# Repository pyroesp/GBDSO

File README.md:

# GBDSO

GBDSO Website : http://swelectronics.co.uk/Gameboy/DsoDemo/DsoDemo.htm  
GBDSO Elektor article : http://www.radanpro.com/Radan2400/TestShematics/GameBoyScope.pdf  
GBDSO BOM list (2019/02) : https://docs.google.com/spreadsheets/d/1vu9Xc1Mw5STfz_mAsAOrmmyRrHJMRS4_JKM7iif-KBE/edit#gid=0  

## Max Voltage Ratings

- +/- 16V on 1:1  
- +/- 50V on 10:1  

Do **NOT** exceed the max voltage ratings or you risk damaging the cartridge and the Game Boy.  
I'm not responsible if it blows up!  

## Schematic

## PCB

## Game Boy test

Since the big v2 update on 2021/01/08, this GBDSO board works on both channels.  
See pictures below:  

## Official game cart dimensions

Below you'll find the dimensions for the PCB of an official game (Pokémon Yellow JAP).  

## Programming the AT27C256R

The first jumper JP1 selects either 5V to pin 2 of the PROM (VPP) and VPP from the unused 5th edge connector.  

The second jumper JP2 cuts the power going to the rest of the board.  
While in programming mode, the PROM needs 6.5V to VCC and I'd rather not have it power to the rest of the board.  

To program the PROM, leave JP2 open and set JP1 so that the edge connector VPP is connected to the PROM VPP.  
When programming is done, bridge JP2 and set JP1 so that 5V go to the PROM VPP.  

## GBDSO PROM to PDIP28  

Any decent Universal Programmer should be able to program the PROM on the cart.  
You can see the adapter board on the 3D rendered board above.  

The Game Boy connector uses the Xunbeifang GNI172 footprint made by **obskyr** from the <a href="https://github.com/gbdev/awesome-gbdev">gbdev discord</a>.  
You can find other Game Boy connectors made by **Gekkio** here: <a href="https://github.com/Gekkio/gekkio-kicad-libs">gekkio-kicad-libs</a>.  

The Xunbeifang GNI172 can be found on <a href="https://www.aliexpress.com/item/For-Nintendo-DS-NDSL-GBA-Game-Cartridge-Card-Reader-Slot-Repair-Part/32679592016.html">aliexpress</a>.

To program the PROM, leave JP1 open and close JP2 as shown below.

Plug the adapter board into a Universal Programmer and set the target device to DIP28 AT27C256R.

Note: This part of the board has not been tested yet, so I hope it works.

## Original GBDSO

Original GBDSO pictures from November 2000 courtesy of **Tauwasser** on the <a href="https://github.com/gbdev/awesome-gbdev">gbdev discord</a>.

## BOM list

|                       Label                        |               Value / Name               | Price per unit | Number | Total Price |                                                     Link                                                     |
|----------------------------------------------------|------------------------------------------|----------------|--------|-------------|--------------------------------------------------------------------------------------------------------------|
| R1, R2, R4, R8, R9, R11                                 | 1M                                       |           0.09 |      6 |        0.54 | https://www.digikey.be/product-detail/en/bourns-inc/CR0805-FX-1004ELF/CR0805-FX-1004ELFCT-ND/3740924         |
| R15                                                | 15k                                      |           0.09 |      1 |        0.09 | https://www.digikey.be/product-detail/en/bourns-inc/CR0805-FX-1502ELF/CR0805-FX-1502ELFCT-ND/3740926         |
| R5, R12                                             | 470k                                     |           0.09 |      2 |        0.18 | https://www.digikey.be/product-detail/en/RC0805FR-07470KL/311-470KCRCT-ND/730924/?itemSeq=284203171          |
| R3, R6, R7, R10, R13, R14                               | 4k7                                      |           0.09 |      6 |        0.54 | https://www.digikey.be/product-detail/en/CR0805-FX-4701ELF/CR0805-FX-4701ELFCT-ND/3925402/?itemSeq=284203192 |
| R16, R17                                            | 100k                                     |           0.09 |      2 |        0.18 | https://www.digikey.be/product-detail/en/yageo/RC0805FR-07100KL/311-100KCRCT-ND/730491                       |
| P1, P2                                              | 100k                                     |           0.24 |      2 |        0.48 | https://www.digikey.be/product-detail/en/bourns-inc/TC33X-2-104E/TC33X-104ECT-ND/612912                      |
| C1, C10                                             | 18p                                      |           0.12 |      2 |        0.24 | https://www.digikey.be/product-detail/en/yageo/CC0805JRNPO9BN180/311-1102-1-ND/303012                        |
| C2, C4, C5, C8, C9, C11, C12, C14, C17-C21, C23, C27, C29, C30 | 100n                                     |           0.09 |     17 |        1.53 | https://www.digikey.be/product-detail/en/CL21B104KBCNNNC/1276-1003-1-ND/3889089/?itemSeq=284204783           |
| C3, C13                                             | 1p8                                      |           0.09 |      2 |        0.18 | https://www.digikey.be/product-detail/en/samsung-electro-mechanics/CL21C1R8CBANNNC/1276-2599-1-ND/3890685    |
| C6, C15                                             | 15p                                      |            0.1 |      2 |         0.2 | https://www.digikey.be/product-detail/en/wurth-electronics-inc/885012007052/732-7847-1-ND/5454474            |
| C7, C16                                             | 220p                                     |           0.09 |      2 |        0.18 | https://www.digikey.be/product-detail/en/CL21B221KBANNNC/1276-2474-1-ND/3890560/?itemSeq=284205074           |
| C22, C24, C25, C26, C28, C31, C33                        | 10µ 16V                                  |           0.31 |      7 |        2.17 | https://www.digikey.be/product-detail/en/vishay-sprague/293D106X0016A2TE3/718-1956-1-ND/3985805              |
| L1, L2, L3                                           | 100µ                                     |           0.18 |      3 |        0.54 | https://www.digikey.be/product-detail/en/taiyo-yuden/LBM2016T101J/587-1817-1-ND/1465287                      |
| D1, D2                                              | BAV199                                   |           0.17 |      2 |        0.34 | https://www.digikey.be/product-detail/en/diodes-incorporated/BAV199-7-F/BAV199-FDICT-ND/1033647              |
| D3                                                 | ZR25D01 -> ZR40402F25TA                  |           0.61 |      1 |        0.61 | https://www.digikey.be/product-detail/en/diodes-incorporated/ZR40402F25TA/ZR40402F25TACT-ND/243209           |
| IC1, IC3                                            | MC33182D -> TL072CDT                     |           0.42 |      2 |        0.84 | https://www.digikey.com/product-detail/en/stmicroelectronics/TL072CDT/497-2200-1-ND/599107                   |
| IC2                                                | DS1267S100 -> DS1267BS-100+              |           5.52 |      1 |        5.52 | https://www.digikey.be/product-detail/en/maxim-integrated/DS1267BS-100/DS1267BS-100-ND/5049982               |
| IC4                                                | MAX114CAG                                |            6.9 |      1 |         6.9 | https://www.digikey.be/product-detail/en/maxim-integrated/MAX114CAG/MAX114CAG-ND/1428095                     |
| IC5                                                | 74HC175D                                 |           0.41 |      1 |        0.41 | https://www.digikey.be/product-detail/en/texas-instruments/SN74HC175DR/296-14840-1-ND/562676                 |
| IC6                                                | 74HC138D                                 |           0.34 |      1 |        0.34 | https://www.digikey.be/product-detail/en/texas-instruments/SN74HC138D/296-1193-5-ND/277220                   |
| IC7                                                | AT27C256R-12JC -> AT27C256R-70JU         |            1.2 |      1 |         1.2 | https://www.digikey.be/product-detail/en/microchip-technology/AT27C256R-70JU/AT27C256R-70JU-ND/1008583       |
| IC8                                                | TLC27L2CD                                |           0.86 |      1 |        0.86 | https://www.digikey.be/product-detail/en/texas-instruments/TLC27L2CDR/296-1316-1-ND/404950                   |
| IC9                                                | MAX828EUK                                |            4.5 |      1 |         4.5 | https://www.digikey.be/product-detail/en/MAX828EUK%2bT/MAX828EUK%2bTCT-ND/2699369/?itemSeq=284207452         |
| S1, S2                                              | Slide switch 1 change-over contact |           0.49 |      2 |        0.98 | https://www.digikey.be/product-detail/en/c-k/JS102011SAQN/401-1999-1-ND/1640114                              |
| K1, K2                                              | 3.5mm stereo socket -> mono smd          |           0.88 |      2 |        1.76 | https://www.digikey.be/product-detail/en/cui-inc/MJ-3523-SMT-TR/CP-3523MJCT-ND/669691                        |

Total Price: 31.31€<br>			
Total Components: 70

## Replacement parts

The input opamps MC33182D is not being sold anymore, at least not on digikey.  
So looking around I thought the TL062 would be a nice replacement but the numbers weren't quite similar.  
I've looked at the TL072 and this one looks pretty good, the only downside is that it isn't a low power opamp.  

If we compare the current consumption from the TL072 and the MC33182D, the TL072 uses 5 times more current (1.4mA typ.) than the MC33182D (420µA).  

Looking further into the MC33182D I found this old forum post talking about replacing it on a GBDSO : [edaboard forum](https://www.edaboard.com/showthread.php?40716-Need-alternative-for-MC33182D-(dual-opamp)-for-GBDSO&highlight=gbdso)  
They talked about the TL082, LF412, TLE2082A and TLE2602. Someone used that last one as a replacement for the MC33182D, although digikey has it priced at around 2$ per unit...  

Looking at the information page on TI's website, this is what they say:  
> The TL206x devices are pin-compatible with other TI BiFETs; they can be used to double the bandwidth of TL06x and TL03x circuits, or to reduce power consumption of TL05x, TL07x, and TL08x circuits by nearly 90%.  

That power reduction is crucial for long lasting batteries.  
For now though, I'll try the TL062 I currently have and will try the TL072 on a later date.  
I'll also try to find a suitable, pin-compatible, low power replacement opamp for the TL072.

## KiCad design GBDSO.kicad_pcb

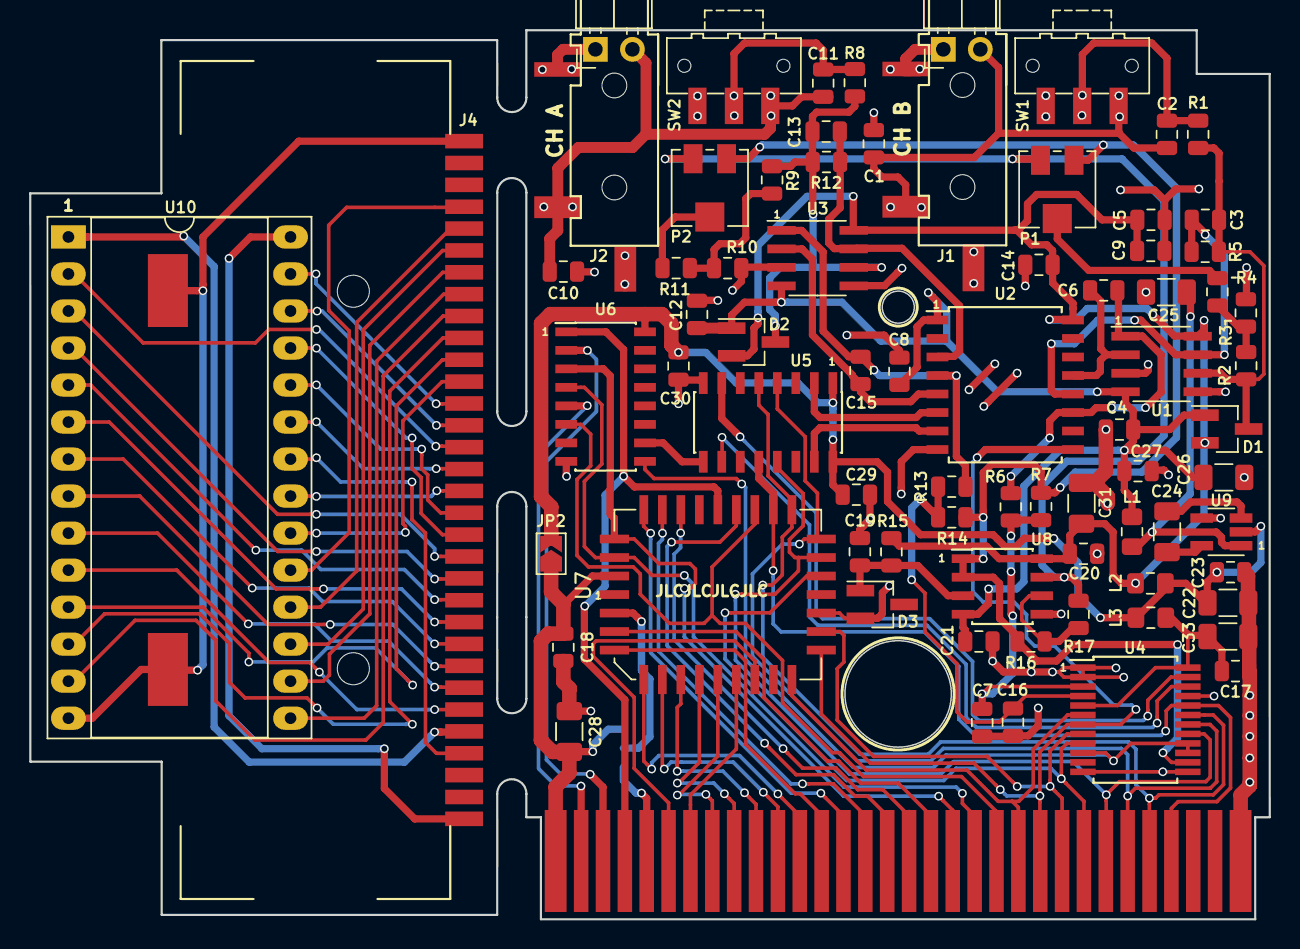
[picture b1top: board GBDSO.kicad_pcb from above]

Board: 2 copper layers, 85.0 x 61.0 mm, 77 parts (1 on the bottom side), 92 nets.

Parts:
C1, C10: 18p; C_0805_2012Metric
C2, C4, C5, C8, C9, C11, C12, C14, C17, C18, C19, C20, C21, C23, C27, C29, C30: 100n; C_0805_2012Metric
C3, C13: 1p8; C_0805_2012Metric
C6, C15: 15p; C_0805_2012Metric
C7, C16: 220p; C_0805_2012Metric
C22, C24, C25, C26, C28, C31, C33: 10µ; C_1206_3216Metric
D1, D2: BAV199; SOT-23_Handsoldering
D3: ZR4040-2.5; SOT-23_Handsoldering
J1, J2: MJ-3523-SMT-TR
J3: EdgeConnector; GB_EdgeConnector
J4: GameBoy Cartridge Connector; Game_Boy_Cartridge_Slot_Xunbeifang_GNI172
J5, J6: Conn_01x02; PinHeader_1x02_P2.54mm_Horizontal
JP1: SolderJumper_3_Open; SolderJumper-3_P1.3mm_Open_RoundedPad1.0x1.5mm_NumberLabels
JP2: SolderJumper_2_Open; SolderJumper-2_P1.3mm_Open_TrianglePad1.0x1.5mm
L1, L2, L3: 100µ; L_0805_2012Metric_Pad1.15x1.40mm_HandSolder
P1, P2: 100k; Potentiometer_Vishay_TS53YJ_Vertical
R1, R2, R4, R8, R9, R11: 1M; R_0805_2012Metric
R3, R6, R7, R10, R13, R14: 4k7; R_0805_2012Metric
R5, R12: 470k; R_0805_2012Metric
R15: 15k; R_0805_2012Metric
R16, R17: 100k; R_0805_2012Metric
SW1, SW2: SW_SPDT; SW_SPDT_CK-JS102011SAQN
U1, U3: TL072; SOIC-8_3.9x4.9mm_P1.27mm
U2: DS1267_SOIC; SOIC-16W_7.5x10.3mm_P1.27mm
U4: MAX114CAG; SSOP-24_5.3x8.2mm_P0.65mm
U5: 74HC175D; SOIC-16_3.9x9.9mm_P1.27mm
U6: 74HC138D; SOIC-16_3.9x9.9mm_P1.27mm
U7: AT27C256R; PLCC-32_HandSolder
U8: TLC272; SOIC-8_3.9x4.9mm_P1.27mm
U9: MAX828; SOT-23-5_HandSoldering
U10: AT27C256R-PDIP28; DIP-28_W15.24mm_Socket_LongPads

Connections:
+2.5V: P1.3, P2.3, R7.2, R14.2, R16.2, U4.14, U8.1, U8.2
+5V: C18.1, C22.1, C23.1, C28.1, C29.1, C30.1, J3.1, JP1.3, JP2.1, JP2.2, L2.1, L3.1, U5.1, U5.16, U6.16, U7.32, U9.2
+5VA: C5.1, C9.1, C14.1, C20.1, C31.1, D1.2, D2.2, L2.2, R15.2, U1.8, U2.16, U3.8, U8.8
+5VC: C17.1, C33.1, L3.2, U4.5, U4.24
-2.5V: P1.1, P2.1, R17.1, U8.7
-5V: C4.2, C8.1, C12.2, C21.1, C26.1, C27.1, D1.1, D2.1, L1.2, U1.4, U2.1, U3.4, U8.4
/GBDSO Cartridge/A0: J3.6, U7.11
/GBDSO Cartridge/A1: J3.7, U7.10
/GBDSO Cartridge/A2: J3.8, U7.9
/GBDSO Cartridge/A3: J3.9, U7.8
/GBDSO Cartridge/A4: J3.10, U7.7
/GBDSO Cartridge/A5: J3.11, U7.6
/GBDSO Cartridge/A6: J3.12, U7.5
/GBDSO Cartridge/A7: J3.13, U7.4
/GBDSO Cartridge/A8: J3.14, U7.29
/GBDSO Cartridge/A9: J3.15, U7.28
/GBDSO Cartridge/A10: J3.16, U7.24
/GBDSO Cartridge/A11: J3.17, U7.27
/GBDSO Cartridge/A12: J3.18, U7.3
/GBDSO Cartridge/A13: J3.19, U6.3, U7.30
/GBDSO Cartridge/A14: J3.20, U6.4, U7.31
/GBDSO Cartridge/A15: J3.21, U6.6, U7.23
/GBDSO Cartridge/D0: J3.22, U4.6, U7.13
/GBDSO Cartridge/D1: J3.23, U2.9, U4.7, U7.14
/GBDSO Cartridge/D2: J3.24, U4.8, U7.15
/GBDSO Cartridge/D3: J3.25, U4.9, U7.18
/GBDSO Cartridge/D4: J3.26, U4.17, U5.13, U7.19
/GBDSO Cartridge/D5: J3.27, U4.18, U5.4, U7.20
/GBDSO Cartridge/D6: J3.28, U4.19, U5.5, U7.21
/GBDSO Cartridge/D7: J3.29, U4.20, U5.12, U7.22
/GBDSO Cartridge/ECLK: J3.2, U6.5
/GBDSO Cartridge/VPP: J3.5, JP1.1
/GBDSO Cartridge/~RD: J3.4, U6.1, U7.25
/GBDSO Cartridge/~WR: J3.3, U6.2
/GBDSO EPROM Adapter Board/A0: J4.6, U10.10
/GBDSO EPROM Adapter Board/A1: J4.7, U10.9
/GBDSO EPROM Adapter Board/A2: J4.8, U10.8
/GBDSO EPROM Adapter Board/A3: J4.9, U10.7
/GBDSO EPROM Adapter Board/A4: J4.10, U10.6
/GBDSO EPROM Adapter Board/A5: J4.11, U10.5
/GBDSO EPROM Adapter Board/A6: J4.12, U10.4
/GBDSO EPROM Adapter Board/A7: J4.13, U10.3
/GBDSO EPROM Adapter Board/A8: J4.14, U10.25
/GBDSO EPROM Adapter Board/A9: J4.15, U10.24
/GBDSO EPROM Adapter Board/A10: J4.16, U10.21
/GBDSO EPROM Adapter Board/A11: J4.17, U10.23
/GBDSO EPROM Adapter Board/A12: J4.18, U10.2
/GBDSO EPROM Adapter Board/A13: J4.19, U10.26
/GBDSO EPROM Adapter Board/A14: J4.20, U10.27
/GBDSO EPROM Adapter Board/A15: J4.21, U10.20
/GBDSO EPROM Adapter Board/D0: J4.22, U10.11
/GBDSO EPROM Adapter Board/D1: J4.23, U10.12
/GBDSO EPROM Adapter Board/D2: J4.24, U10.13
/GBDSO EPROM Adapter Board/D3: J4.25, U10.15
/GBDSO EPROM Adapter Board/D4: J4.26, U10.16
/GBDSO EPROM Adapter Board/D5: J4.27, U10.17
/GBDSO EPROM Adapter Board/D6: J4.28, U10.18
/GBDSO EPROM Adapter Board/D7: J4.29, U10.19
/GBDSO EPROM Adapter Board/VCC: J4.1, U10.28
/GBDSO EPROM Adapter Board/VPP: J4.5, U10.1
/GBDSO EPROM Adapter Board/~RD: J4.4, U10.22
GND: C1.2, C4.1, C5.2, C7.2, C8.2, C9.2, C10.2, C12.1, C14.2, C16.2, C17.2, C18.2, C19.2, C20.2, C21.2, C22.2, C23.2, C25.2, C26.2, C27.2, C28.2, C29.2, C30.2, C31.2, C33.2, D3.2, J1.1, J2.1, J3.32, J4.32, J5.1, J6.1, R3.1, R10.1, U1.3, U1.5, U2.8, U3.3, U3.5, U4.1, U4.2, U4.12, U4.13, U4.21, U5.8, U6.8, U7.16, U8.5, U9.4, U10.14
unnamed: C1.1, C2.1, J1.2, J5.2, SW1.1
unnamed: C2.2, R1.2, SW1.2
unnamed: C3.1, D1.3, R1.1, R2.2, R5.2, U1.6
unnamed: C3.2, R5.1, U1.7, U2.12
unnamed: C6.1, U1.2, U2.13
unnamed: C6.2, R6.2, U1.1, U2.11
unnamed: C7.1, R6.1, R7.1, U4.3
unnamed: C10.1, C11.2, J2.2, J6.2, SW2.1
unnamed: C11.1, R8.2, SW2.2
unnamed: C13.1, D2.3, R8.1, R9.2, R12.2, U3.6
unnamed: C13.2, R12.1, U2.3, U3.7
unnamed: C15.1, R13.2, U2.4, U3.1
unnamed: C15.2, U2.5, U3.2
unnamed: C16.1, R13.1, R14.1, U4.4
unnamed: C19.1, D3.1, R15.1, U8.3
unnamed: C24.1, U9.5
unnamed: C24.2, U9.3
unnamed: C25.1, L1.1, U9.1
unnamed: JP1.2, U7.2
unnamed: P1.2, R4.1
unnamed: P2.2, R11.1
unnamed: R2.1, R3.2, R4.2
unnamed: R9.1, R10.2, R11.2
unnamed: R16.1, R17.2, U8.6
unnamed: U2.6, U5.2
unnamed: U2.7, U5.15
unnamed: U4.10, U4.15, U4.16, U6.9
unnamed: U4.22, U5.10
unnamed: U4.23, U5.7
unnamed: U5.9, U6.10

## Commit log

2019-02-11 added ignore list
2019-02-11 add component libraries
2019-02-11 added sym-lib-table file
2019-02-11 added project, schematic, netlist and PCB files
2019-02-11 made the BAV199 diodes smaller
2019-02-11 minor update to voltage reference component
2019-02-11 cache file
2019-02-11 update symbole table and add footprint table
2019-02-11 updated schematic
2019-02-11 add new component : SMD mono 3.5mm jack
2019-02-11 update git ignore
2019-02-11 dcm file holds descriptions, aliases, keywords for lib symbols
2019-02-11 updated pcb with new and all footprints
2019-02-11 generated new netlist
2019-02-12 finished schematic, need to double check to be sure
2019-02-12 generated netlist
2019-02-12 updated pcb
2019-02-13 updated schematic, corrected some errors
2019-02-13 new generated netlist
2019-02-15 updated PCB, changed track width, started with routing power and GND. Also, bottom layer is a GND plane
2019-02-16 update footprint table
2019-02-16 update cache lib
2019-02-16 update footprint audio jack
2019-02-16 updated schematic, new generated netlist, finished pcb
2019-02-16 created new footprint for GB edge connector
2019-02-16 add images of PCB and schematic
2019-02-16 final update of pcb, updated images
2019-02-16 generated gerber files for production
2019-02-16 updated ignore list
2019-02-21 cropped the image
2019-02-21 added orignal PCB pictures, courtesy of Tauwasser from gbdev discord, see readme
2019-02-21 renamed file GB-DSO_B to GBDSO_B
2019-02-21 fixing breaks/new lines
2019-02-21 fixed typo in bom list
2019-03-04 added cache dcm file
2019-03-04 general update and lib fix + new generated gerber
2019-03-05 added jumpers to the schematic and pcb so that the EPROM can be programmed on the cartridge
2019-03-05 updated schematic with jumpers
2019-03-05 updated file with new jumpers (forgot to include in previous commit)
2019-03-05 updated readme with information about programming the EPROM on the board + added a few images showing the jumpers and EPROM.
2019-03-05 updated pcb images with new jumpers
2019-03-05 updated gerber and drill files
2019-03-05 trying to fix table
2019-03-06 forgot to add pin 12 and 26 (NC) to the component, now fixed
2019-03-06 added wide PDIP28 version of the eprom to the library
2019-03-06 new gerber and drill files
2019-03-06 updated readme and added/updated pictures
2019-03-06 updated readme + added schematic-2.png
2019-03-06 updated schematic (now 2 pages) and PCB + adding Gekkio DS Lite footprint
2019-03-06 changed GameBoy cart on the adapter board from Gekkio's footprint to Xunbeifang GNI172 footprint made by obskyr
2019-03-06 updated gerber with new Xunbeifang GB connector
2019-03-06 updated schematic, pcb, pictures and readme because I changed the GB connector to the Xunbeifang one
2019-03-06 added link to buy xunbeifang connector in readme
2019-03-06 removed gekkio GB connector, now using Xunbeifang GNI172 connector
2019-03-06 bom list has been moved to the bottom of the readme
2019-03-07 fixed edge cuts
2019-03-07 generated new gerber files after fixing edge cuts
2019-03-07 updated readme and added v0 PCB picture
2019-03-07 changed picture from jpg to png
2019-03-07 cleanup, moving stuff in folder, updating readme and schematic files
2019-03-07 added plcc32 package, update board with new 3D package
2019-03-08 updated readme with official pcb dimensions
2019-03-08 fixed link to first pcb picture
2019-03-08 added freecad file and SVG file for the cartridge dimensions
2019-03-08 added dimensions svg to readme
2019-03-08 removed log stuff from README and put it in LOG.md file
2019-03-08 fixed heading for Log
2019-03-08 added pcb thickness to tech drawing, updated readme
2019-03-09 modify PCB to match the cart dimensions, update all gerber files, update PCB pictures
2019-03-09 updated LOG file with freecad issue loading the tracks
2019-03-10 renamed file due to typo, moved files to dedicated folder
2019-03-10 added render of the usage of the adapter board + updated readme with pictures
2019-03-10 updated readme with max voltage ratings
2019-03-10 modified the pads from custom to rectangular, because loading the pcb into freecad triggered an exception
2019-03-10 minor updates
2019-03-10 updated todo list
2019-03-10 fixed link to image
2019-03-10 new generated gerber files
2019-03-24 added gbdso website to readme
2019-03-24 fix formatting
2019-04-18 increased the size of the pads to make it easier to solder
2019-04-18 Bunch of changes: fixed pin swap on DS1267_SOIC, fixed footprint of all uncorrect ICs, fixed footprint off the three inductors as they were too big. Because of the size change of the footprint of the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
2019-04-19 Fixed wrong measurement in tech drawing
2019-04-19 Moved small hole to correct position, also had to move C8 and the -5V trace because of the hole.
2019-04-20 updated gerber files with latest fixes/improvements to the PCB
2019-04-20 added some comments to the log file
2019-04-24 pcb v1 pictures
2020-04-02 changed TL062 to TL072, see #14. updated schematic image, see #9.
2020-04-02 Changed TL062 to TL072, #14. Added silkscreen for channels, #8. Updated PCB images, #11
2020-04-02 file updated after save
2020-04-03 moved C4, C5, C12, C14 to the power pins of the TL072
2020-04-04 fix #16
2020-04-04 fix #17
2020-04-04 issue #16, #17 and #18 are fixed in the schematic but not yet in the PCB
    reopened issue #16 and #17 as they were not yet fixed in the PCB
2020-04-04 fix #16, fix #17, fix #18 in schematic and PCB
    fixed issues #16, #17, #18 in schematic and PCB, with improvement here and there.
2020-04-05 added chapter replacement parts to the readme
2020-04-05 made a hand soldered version of the PLCC32 footprint
2020-04-05 Used the new PLCC32 handsolder footprint and moved a few traces around
2020-12-25 updated gerber
2020-12-25 fixed voltage divider at input buffer
    R3-R4, R10-R11 were swapped
2020-12-25 added some art and fixed the resistors R3-R4/R10-R11
2020-12-25 updated gerber files
2020-12-25 small update
2020-12-25 increased tab with to 4mm as recommended by jlcpcb eng + updated gerber
2020-12-25 minor update
2021-01-08 big v2 update, hopefully everything is ok now
2021-01-08 added GB pics of the GBDSO working
2021-01-24 added assembled image
2021-01-28 ROM file for the AT27C256
    with permission from Elektor/original author
2021-01-30 rom publishing permission emails
